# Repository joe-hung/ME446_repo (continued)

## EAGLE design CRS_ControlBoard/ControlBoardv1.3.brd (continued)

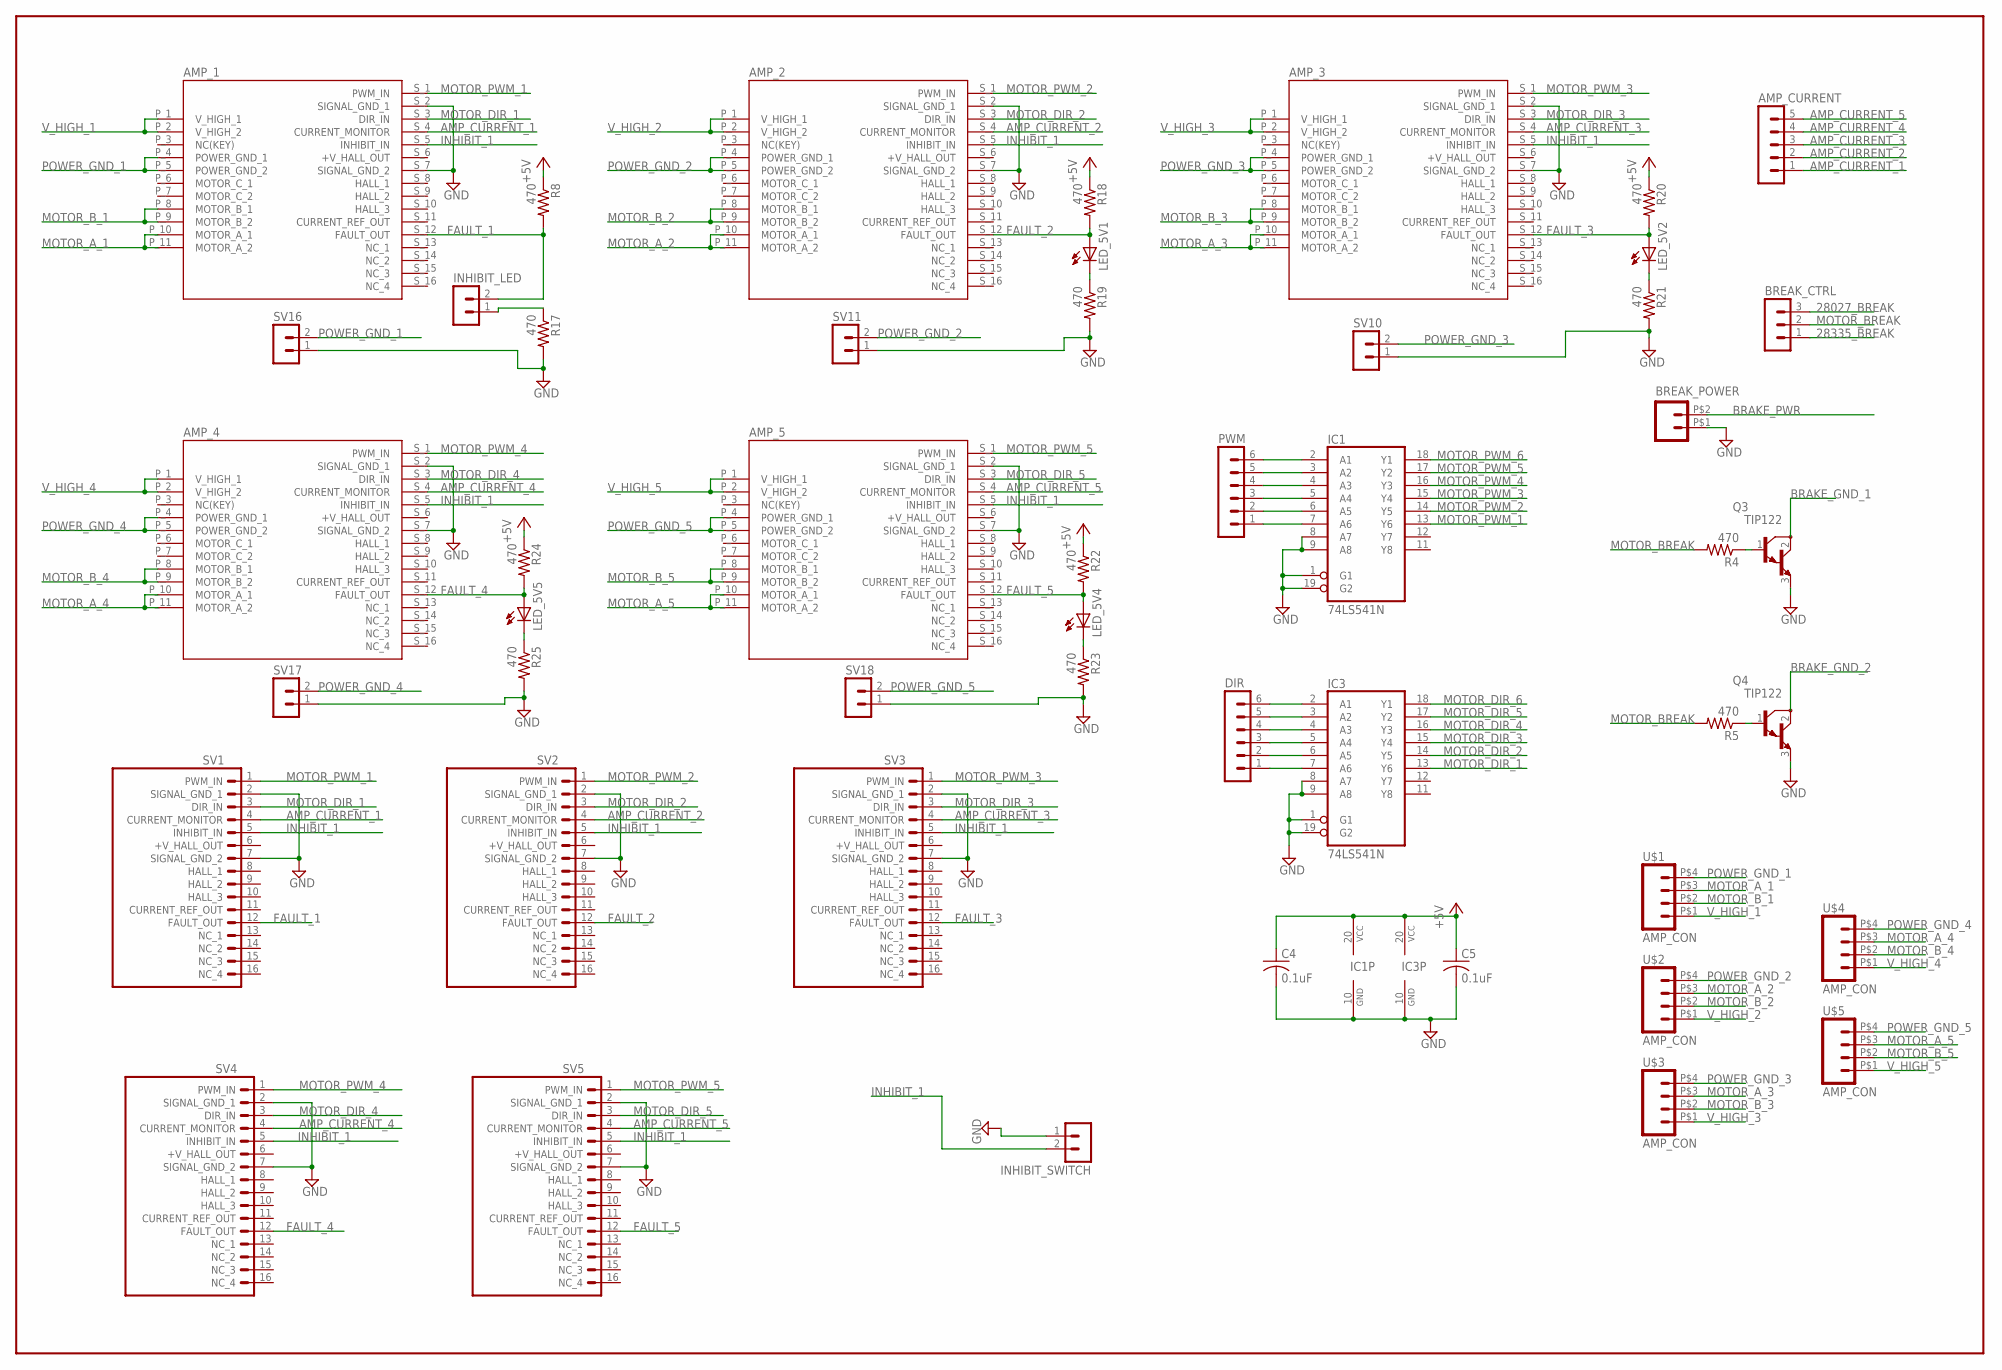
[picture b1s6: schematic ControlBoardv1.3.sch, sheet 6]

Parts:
AMP_1, AMP_2, AMP_3, AMP_4, AMP_5: AZBDC12A8THROUGH_HOLE; AZBDC12A8
AMP_CURRENT: MA05-1
BREAK_CTRL: MA03-1
BREAK_POWER: BREAK_POWER_CON
C4, C5: 0.1uF; C1206
DIR: MA06-1
IC1, IC3: 74LS541N; DIL20
INHIBIT_LED: MA02-1
INHIBIT_SWITCH: MA02-1
LED_5V1, LED_5V2, LED_5V4, LED_5V5: LED3MM
PWM: MA06-1
Q3, Q4: TIP122; TO220
R4, R5, R8, R17, R18, R19, R20, R21, R22, R23, R24, R25: 470; M1206
SV1, SV2, SV3, SV4, SV5: AMP_HEADER
SV10, SV11, SV16, SV17, SV18: MA02-1
U$1, U$2, U$3, U$4, U$5: AMP_CON; APM_CON

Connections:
28027_BREAK: BREAK_CTRL.3; also elsewhere on the board
28335_BREAK: BREAK_CTRL.1; also elsewhere on the board
+5V: C4.1, C5.1, IC1.20 (VCC), IC3.20 (VCC), R8.1, R18.1, R20.1, R22.1, R24.1; also elsewhere on the board
AMP_CURRENT_1: AMP_1.S_4 (CURRENT_MONITOR), AMP_CURRENT.1, SV1.4 (CURRENT_MONITOR)
AMP_CURRENT_2: AMP_2.S_4 (CURRENT_MONITOR), AMP_CURRENT.2, SV2.4 (CURRENT_MONITOR)
AMP_CURRENT_3: AMP_3.S_4 (CURRENT_MONITOR), AMP_CURRENT.3, SV3.4 (CURRENT_MONITOR)
AMP_CURRENT_4: AMP_4.S_4 (CURRENT_MONITOR), AMP_CURRENT.4, SV4.4 (CURRENT_MONITOR)
AMP_CURRENT_5: AMP_5.S_4 (CURRENT_MONITOR), AMP_CURRENT.5, SV5.4 (CURRENT_MONITOR)
BRAKE_GND_1: Q3.2 (C); also elsewhere on the board
BRAKE_GND_2: Q4.2 (C); also elsewhere on the board
BRAKE_PWR: BREAK_POWER.P$2; also elsewhere on the board
FAULT_1: AMP_1.S_12 (FAULT_OUT), INHIBIT_LED.2, R8.2, SV1.12 (FAULT_OUT)
FAULT_2: AMP_2.S_12 (FAULT_OUT), LED_5V1.A, R18.2, SV2.12 (FAULT_OUT)
FAULT_3: AMP_3.S_12 (FAULT_OUT), LED_5V2.A, R20.2, SV3.12 (FAULT_OUT)
FAULT_4: AMP_4.S_12 (FAULT_OUT), LED_5V5.A, R24.2, SV4.12 (FAULT_OUT)
FAULT_5: AMP_5.S_12 (FAULT_OUT), LED_5V4.A, R22.2, SV5.12 (FAULT_OUT)
GND: AMP_1.S_2 (SIGNAL_GND_1), AMP_1.S_7 (SIGNAL_GND_2), AMP_2.S_2 (SIGNAL_GND_1), AMP_2.S_7 (SIGNAL_GND_2), AMP_3.S_2 (SIGNAL_GND_1), AMP_3.S_7 (SIGNAL_GND_2), AMP_4.S_2 (SIGNAL_GND_1), AMP_4.S_7 (SIGNAL_GND_2), AMP_5.S_2 (SIGNAL_GND_1), AMP_5.S_7 (SIGNAL_GND_2), BREAK_POWER.P$1, C4.2, C5.2, IC1.1 (G1), IC1.8 (A7), IC1.9 (A8), IC1.10 (GND), IC1.19 (G2), IC3.1 (G1), IC3.8 (A7), IC3.9 (A8), IC3.10 (GND), IC3.19 (G2), INHIBIT_SWITCH.1, Q3.3 (E), Q4.3 (E), R17.2, R19.2, R21.2, R23.2, R25.2, SV1.2 (SIGNAL_GND_1), SV1.7 (SIGNAL_GND_2), SV2.2 (SIGNAL_GND_1), SV2.7 (SIGNAL_GND_2), SV3.2 (SIGNAL_GND_1), SV3.7 (SIGNAL_GND_2), SV4.2 (SIGNAL_GND_1), SV4.7 (SIGNAL_GND_2), SV5.2 (SIGNAL_GND_1), SV5.7 (SIGNAL_GND_2), SV10.1, SV11.1, SV16.1, SV17.1, SV18.1; also elsewhere on the board
INHIBIT_1: AMP_1.S_5 (INHIBIT_IN), AMP_2.S_5 (INHIBIT_IN), AMP_3.S_5 (INHIBIT_IN), AMP_4.S_5 (INHIBIT_IN), AMP_5.S_5 (INHIBIT_IN), INHIBIT_SWITCH.2, SV1.5 (INHIBIT_IN), SV2.5 (INHIBIT_IN), SV3.5 (INHIBIT_IN), SV4.5 (INHIBIT_IN), SV5.5 (INHIBIT_IN)
MOTOR_A_1: AMP_1.P_10 (MOTOR_A_1), AMP_1.P_11 (MOTOR_A_2), U$1.P$3
MOTOR_A_2: AMP_2.P_10 (MOTOR_A_1), AMP_2.P_11 (MOTOR_A_2), U$2.P$3
MOTOR_A_3: AMP_3.P_10 (MOTOR_A_1), AMP_3.P_11 (MOTOR_A_2), U$3.P$3
MOTOR_A_4: AMP_4.P_10 (MOTOR_A_1), AMP_4.P_11 (MOTOR_A_2), U$4.P$3
MOTOR_A_5: AMP_5.P_10 (MOTOR_A_1), AMP_5.P_11 (MOTOR_A_2), U$5.P$3
MOTOR_BREAK: BREAK_CTRL.2, R4.2, R5.2
MOTOR_B_1: AMP_1.P_8 (MOTOR_B_1), AMP_1.P_9 (MOTOR_B_2), U$1.P$2
MOTOR_B_2: AMP_2.P_8 (MOTOR_B_1), AMP_2.P_9 (MOTOR_B_2), U$2.P$2
MOTOR_B_3: AMP_3.P_8 (MOTOR_B_1), AMP_3.P_9 (MOTOR_B_2), U$3.P$2
MOTOR_B_4: AMP_4.P_8 (MOTOR_B_1), AMP_4.P_9 (MOTOR_B_2), U$4.P$2
MOTOR_B_5: AMP_5.P_8 (MOTOR_B_1), AMP_5.P_9 (MOTOR_B_2), U$5.P$2
MOTOR_DIR_1: AMP_1.S_3 (DIR_IN), IC3.13 (Y6), SV1.3 (DIR_IN)
MOTOR_DIR_2: AMP_2.S_3 (DIR_IN), IC3.14 (Y5), SV2.3 (DIR_IN)
MOTOR_DIR_3: AMP_3.S_3 (DIR_IN), IC3.15 (Y4), SV3.3 (DIR_IN)
MOTOR_DIR_4: AMP_4.S_3 (DIR_IN), IC3.16 (Y3), SV4.3 (DIR_IN)
MOTOR_DIR_5: AMP_5.S_3 (DIR_IN), IC3.17 (Y2), SV5.3 (DIR_IN)
MOTOR_DIR_6: IC3.18 (Y1)
MOTOR_PWM_1: AMP_1.S_1 (PWM_IN), IC1.13 (Y6), SV1.1 (PWM_IN)
MOTOR_PWM_2: AMP_2.S_1 (PWM_IN), IC1.14 (Y5), SV2.1 (PWM_IN)
MOTOR_PWM_3: AMP_3.S_1 (PWM_IN), IC1.15 (Y4), SV3.1 (PWM_IN)
MOTOR_PWM_4: AMP_4.S_1 (PWM_IN), IC1.16 (Y3), SV4.1 (PWM_IN)
MOTOR_PWM_5: AMP_5.S_1 (PWM_IN), IC1.17 (Y2), SV5.1 (PWM_IN)
MOTOR_PWM_6: IC1.18 (Y1)
unnamed: IC1.7 (A6), PWM.1
unnamed: IC1.6 (A5), PWM.2
unnamed: DIR.1, IC3.7 (A6)
unnamed: Q3.1 (B), R4.1
unnamed: DIR.2, IC3.6 (A5)
unnamed: DIR.3, IC3.5 (A4)
unnamed: DIR.4, IC3.4 (A3)
unnamed: IC1.5 (A4), PWM.3
unnamed: IC1.4 (A3), PWM.4
unnamed: IC1.3 (A2), PWM.5
unnamed: IC1.2 (A1), PWM.6
unnamed: INHIBIT_LED.1, R17.1
unnamed: Q4.1 (B), R5.1
unnamed: DIR.6, IC3.2 (A1)
unnamed: DIR.5, IC3.3 (A2)
unnamed: LED_5V1.K (C), R19.1
unnamed: LED_5V2.K (C), R21.1
unnamed: LED_5V4.K (C), R23.1
unnamed: LED_5V5.K (C), R25.1
POWER_GND_1: AMP_1.P_4 (POWER_GND_1), AMP_1.P_5 (POWER_GND_2), SV16.2, U$1.P$4
POWER_GND_2: AMP_2.P_4 (POWER_GND_1), AMP_2.P_5 (POWER_GND_2), SV11.2, U$2.P$4
POWER_GND_3: AMP_3.P_4 (POWER_GND_1), AMP_3.P_5 (POWER_GND_2), SV10.2, U$3.P$4
POWER_GND_4: AMP_4.P_4 (POWER_GND_1), AMP_4.P_5 (POWER_GND_2), SV17.2, U$4.P$4
POWER_GND_5: AMP_5.P_4 (POWER_GND_1), AMP_5.P_5 (POWER_GND_2), SV18.2, U$5.P$4
V_HIGH_1: AMP_1.P_1 (V_HIGH_1), AMP_1.P_2 (V_HIGH_2), U$1.P$1
V_HIGH_2: AMP_2.P_1 (V_HIGH_1), AMP_2.P_2 (V_HIGH_2), U$2.P$1
V_HIGH_3: AMP_3.P_1 (V_HIGH_1), AMP_3.P_2 (V_HIGH_2), U$3.P$1
V_HIGH_4: AMP_4.P_1 (V_HIGH_1), AMP_4.P_2 (V_HIGH_2), U$4.P$1
V_HIGH_5: AMP_5.P_1 (V_HIGH_1), AMP_5.P_2 (V_HIGH_2), U$5.P$1

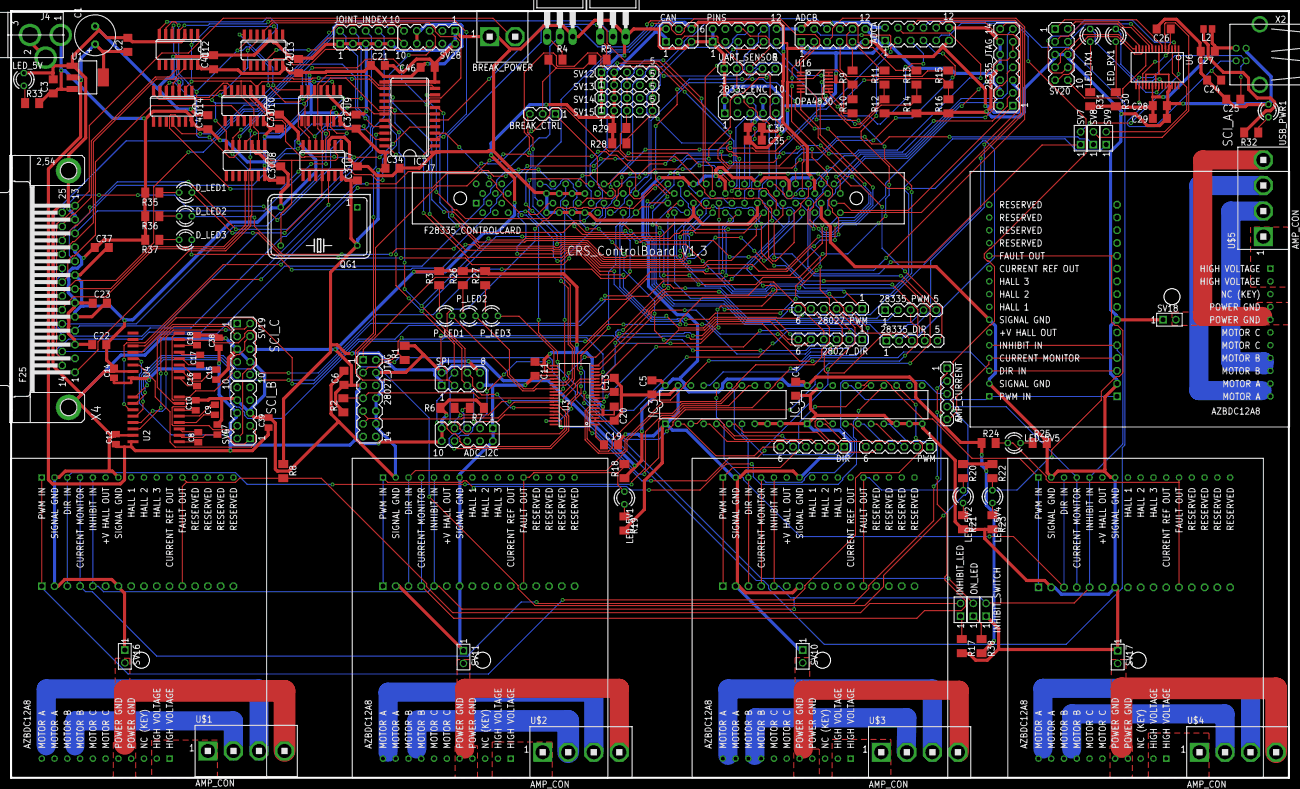
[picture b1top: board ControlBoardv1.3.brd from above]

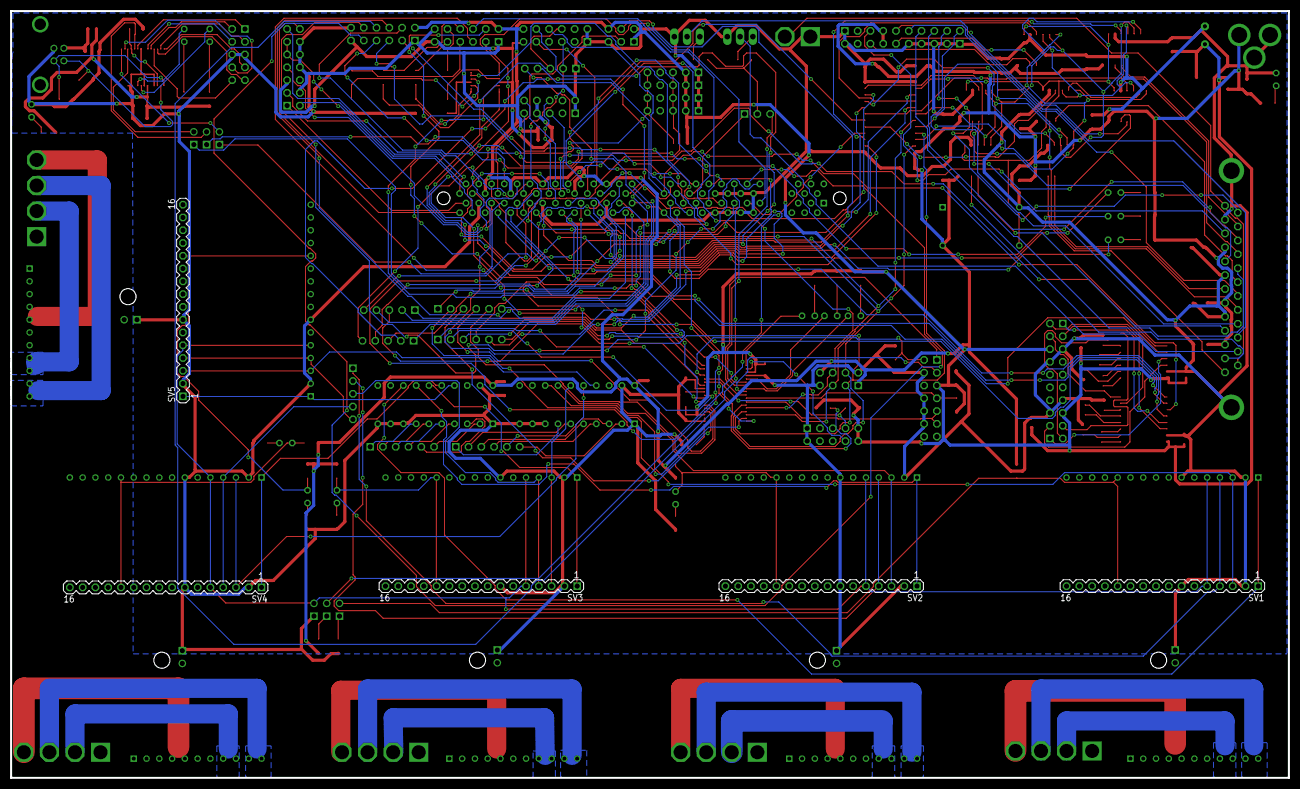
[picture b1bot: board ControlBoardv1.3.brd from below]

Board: 2 copper layers, 254.0 x 152.4 mm, 172 parts (10 on the bottom side), 249 nets.

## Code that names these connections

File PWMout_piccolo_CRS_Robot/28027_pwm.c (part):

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	case EPWM1:
		
		EALLOW;
		GpioCtrlRegs.GPAMUX1.bit.GPIO0 = 1;
		EDIS;

		EPwm1Regs.TBPRD = PWM_PR;  // Set to Period for 20Khz carrier
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	case EPWM2:
		
		EALLOW;
		GpioCtrlRegs.GPAMUX1.bit.GPIO2 = 1;
		EDIS;

		EPwm2Regs.TBPRD = PWM_PR;  // Set to Period for 20Khz carrier
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	case EPWM3:
		
		EALLOW;
		GpioCtrlRegs.GPAMUX1.bit.GPIO4 = 1;
		EDIS;

		EPwm3Regs.TBPRD = PWM_PR;  // Set to Period for 20Khz carrier
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	case EPWM4:
		
		EALLOW;
		//GpioCtrlRegs.GPAMUX1.bit.GPIO6 = 1;
		EDIS;

		EPwm4Regs.TBPRD = PWM_PR;  // Set to Period for 20Khz carrier
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
	case EPWM1:
		EALLOW;
		GpioCtrlRegs.GPAMUX1.bit.GPIO0 = 0;
		GpioCtrlRegs.GPAMUX1.bit.GPIO1 = 0;
		GpioDataRegs.GPACLEAR.bit.GPIO0 = 0;
		GpioDataRegs.GPACLEAR.bit.GPIO1 = 0;
		GpioCtrlRegs.GPADIR.bit.GPIO0 = 1;
		GpioCtrlRegs.GPADIR.bit.GPIO1 = 1;
		EDIS;
		

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		EPwm1Regs.AQCTLB.bit.PRD = 2; // Set EPWM1B pin when CTR=PRD

		EALLOW;
		GpioCtrlRegs.GPAMUX1.bit.GPIO0 = 1;
		GpioCtrlRegs.GPAMUX1.bit.GPIO1 = 1;
		EDIS;

		break;
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/*	case EPWM2:
		
		EALLOW;
		GpioCtrlRegs.GPAMUX1.bit.GPIO2 = 1;
		EDIS;

		EPwm2Regs.TBPRD = PWM_PR;  // Set to Period for 20Khz carrier
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	case EPWM3:
		
		EALLOW;
		GpioCtrlRegs.GPAMUX1.bit.GPIO4 = 1;
		EDIS;

		EPwm3Regs.TBPRD = PWM_PR;  // Set to Period for 20Khz carrier
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	case EPWM4:
		
		EALLOW;
		GpioCtrlRegs.GPAMUX1.bit.GPIO6 = 1;
		EDIS;

		EPwm4Regs.TBPRD = PWM_PR;  // Set to Period for 20Khz carrier
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		EALLOW;

		//PWM pins
		GpioCtrlRegs.GPAMUX1.bit.GPIO0 = 1; //set to 1 for pwm
		//GpioDataRegs.GPACLEAR.bit.GPIO0 = 0;
		//GpioCtrlRegs.GPADIR.bit.GPIO0 = 0;

		GpioCtrlRegs.GPAMUX1.bit.GPIO1 = 1; //set to 1 for pwm
		//GpioDataRegs.GPACLEAR.bit.GPIO1 = 0;
		//GpioCtrlRegs.GPADIR.bit.GPIO1 = 0;

		//DIR Pins
		GpioCtrlRegs.GPAMUX1.bit.GPIO6 = 0;
		GpioCtrlRegs.GPADIR.bit.GPIO6 = 1;
		GpioCtrlRegs.GPAMUX1.bit.GPIO7 = 0;
		GpioCtrlRegs.GPADIR.bit.GPIO7 = 1;

		EDIS;

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	case EPWM2:

		EALLOW;
		GpioCtrlRegs.GPAMUX1.bit.GPIO2 = 1; //set to 1 for pwm
		//GpioDataRegs.GPACLEAR.bit.GPIO2 = 0;
		//GpioCtrlRegs.GPADIR.bit.GPIO2 = 0;

		GpioCtrlRegs.GPAMUX1.bit.GPIO3 = 1; //set to 1 for pwm
		//GpioDataRegs.GPACLEAR.bit.GPIO3 = 0;
		//GpioCtrlRegs.GPADIR.bit.GPIO3 = 0;

		//DIR Pins
		GpioCtrlRegs.GPAMUX1.bit.GPIO12 = 0;
		GpioCtrlRegs.GPADIR.bit.GPIO12 = 1;
		GpioCtrlRegs.AIOMUX1.bit.AIO4 = 1;
		GpioCtrlRegs.AIODIR.bit.AIO4 = 1;

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	case EPWM3:

		EALLOW;
		GpioCtrlRegs.GPAMUX1.bit.GPIO4 = 1; //set to 1 for pwm
		//GpioDataRegs.GPACLEAR.bit.GPIO4 = 0;
		//GpioCtrlRegs.GPADIR.bit.GPIO4 = 0;

		GpioCtrlRegs.GPAMUX1.bit.GPIO5 = 1; //set to 1 for pwm
		//GpioDataRegs.GPACLEAR.bit.GPIO5 = 0;
		//GpioCtrlRegs.GPADIR.bit.GPIO5 = 0;

		//PWM Pins
		GpioCtrlRegs.AIOMUX1.bit.AIO6 = 1;
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		EPwm1Regs.CMPA.half.CMPA = val;
		//EPwm1Regs.CMPA.half.CMPAHR = dec;
		if (u >= 0) {
			GpioDataRegs.GPASET.bit.GPIO6 = 1;
		} else {
			GpioDataRegs.GPACLEAR.bit.GPIO6 = 1;
		}
		break;

	case (0x2):
		EPwm1Regs.CMPB = val;
		if (u >= 0) {
			GpioDataRegs.GPASET.bit.GPIO7 = 1;
		} else {
			GpioDataRegs.GPACLEAR.bit.GPIO7 = 1;
		}
		break;

//		EPwm2Regs.CMPA.half.CMPA = val;
//		EPwm2Regs.CMPA.half.CMPAHR = dec;
//		if (u >= 0) {
//			GpioDataRegs.GPASET.bit.GPIO7 = 1;   //High Res PWM
//		} else {
//			GpioDataRegs.GPACLEAR.bit.GPIO7 = 1;
//		}
//
//	break;
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	case (0x3):
			EPwm2Regs.CMPA.half.CMPA = val;
			if (u >= 0) {
				GpioDataRegs.GPASET.bit.GPIO12 = 1;
			} else {
				GpioDataRegs.GPACLEAR.bit.GPIO12 = 1;
			}

		break;
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//		EPwm3Regs.CMPA.half.CMPA = val;
//		EPwm3Regs.CMPA.half.CMPAHR = dec;
//		if (u >= 0) {
//			GpioDataRegs.GPASET.bit.GPIO12 = 1;
//		} else {
//			GpioDataRegs.GPACLEAR.bit.GPIO12 = 1;
//		}
//
//	break;
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
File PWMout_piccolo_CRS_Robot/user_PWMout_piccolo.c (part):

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void Debug3Bits(unsigned int bits) {
	switch (bits) {
	case 0:
		GpioDataRegs.GPACLEAR.bit.GPIO0 = 1;
		GpioDataRegs.GPACLEAR.bit.GPIO2 = 1;
		GpioDataRegs.GPACLEAR.bit.GPIO5 = 1;
		break;
	case 1:
		GpioDataRegs.GPASET.bit.GPIO0 = 1;
		GpioDataRegs.GPACLEAR.bit.GPIO2 = 1;
		GpioDataRegs.GPACLEAR.bit.GPIO5 = 1;
		break;
	case 2:
		GpioDataRegs.GPACLEAR.bit.GPIO0 = 1;
		GpioDataRegs.GPASET.bit.GPIO2 = 1;
		GpioDataRegs.GPACLEAR.bit.GPIO5 = 1;

		break;
	case 3:
		GpioDataRegs.GPASET.bit.GPIO0 = 1;
		GpioDataRegs.GPASET.bit.GPIO2 = 1;
		GpioDataRegs.GPACLEAR.bit.GPIO5 = 1;

		break;
	case 4:
		GpioDataRegs.GPACLEAR.bit.GPIO0 = 1;
		GpioDataRegs.GPACLEAR.bit.GPIO2 = 1;
		GpioDataRegs.GPASET.bit.GPIO5 = 1;

		break;
	case 5:
		GpioDataRegs.GPASET.bit.GPIO0 = 1;
		GpioDataRegs.GPACLEAR.bit.GPIO2 = 1;
		GpioDataRegs.GPASET.bit.GPIO5 = 1;

		break;
	case 6:
		GpioDataRegs.GPACLEAR.bit.GPIO0 = 1;
		GpioDataRegs.GPASET.bit.GPIO2 = 1;
		GpioDataRegs.GPASET.bit.GPIO5 = 1;

		break;
	case 7:
		GpioDataRegs.GPASET.bit.GPIO0 = 1;
		GpioDataRegs.GPASET.bit.GPIO2 = 1;
		GpioDataRegs.GPASET.bit.GPIO5 = 1;

		break;
	default:
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
	EALLOW;

		GpioCtrlRegs.GPBMUX1.bit.GPIO34 = 0;
		GpioDataRegs.GPBCLEAR.bit.GPIO34 = 1;
		GpioCtrlRegs.GPBDIR.bit.GPIO34 = 1;

		GpioCtrlRegs.GPAMUX1.bit.GPIO3 = 0;
		GpioDataRegs.GPACLEAR.bit.GPIO3 = 0;
		GpioCtrlRegs.GPADIR.bit.GPIO3 = 1;

		// Code for sensing Magnet  Commented out to use GPIO5 as debug output
//		GpioCtrlRegs.GPAMUX1.bit.GPIO5 = 0;
//		GpioCtrlRegs.GPADIR.bit.GPIO5 = 0;  // input
//		GpioCtrlRegs.GPAPUD.bit.GPIO5 = 0; // enable pullup on GPIO5
//		GpioCtrlRegs.GPAQSEL1.bit.GPIO5 = 0x2;  // qual on 6 samples
//		GpioCtrlRegs.GPACTRL.bit.QUALPRD0 = 0x20;  // QualPeriod of 32*Sysclkout

		GpioCtrlRegs.GPAMUX1.bit.GPIO0 = 0;
		GpioDataRegs.GPACLEAR.bit.GPIO0 = 1;
		GpioCtrlRegs.GPADIR.bit.GPIO0 = 1;

		GpioCtrlRegs.GPAMUX1.bit.GPIO2 = 0;
		GpioDataRegs.GPACLEAR.bit.GPIO2 = 1;
		GpioCtrlRegs.GPADIR.bit.GPIO2 = 1;

		GpioCtrlRegs.GPAMUX1.bit.GPIO5 = 0;
		GpioDataRegs.GPACLEAR.bit.GPIO5 = 1;
		GpioCtrlRegs.GPADIR.bit.GPIO5 = 1;

		GpioCtrlRegs.AIOMUX1.bit.AIO10 = 1;
		GpioCtrlRegs.AIOMUX1.bit.AIO2 = 1;
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		EALLOW;

			// CS pins GPIOs
			//GpioCtrlRegs.GPAMUX1.bit.GPIO6 = 0;
			GpioCtrlRegs.GPAMUX2.bit.GPIO19 = 0;
			// CS pins Outputs
			//GpioCtrlRegs.GPADIR.bit.GPIO6 = 1;
			GpioCtrlRegs.GPADIR.bit.GPIO19 = 1;
			// CS start hi
			//GpioDataRegs.GPASET.bit.GPIO6 = 1;
			GpioDataRegs.GPASET.bit.GPIO19 = 1;
		
		EDIS;

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		if(errorbits & 0x0400) //spi error
		{

			GpioDataRegs.GPBCLEAR.bit.GPIO34 = 1;	// Set LED1

		}
		else{
			GpioDataRegs.GPBSET.bit.GPIO34 = 1; // Clear LED1
		}
		if(errorbits & 0x0100) //lg error
		{
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		{

			GpioDataRegs.AIOCLEAR.bit.AIO2 = 1;	// Set LED4
			GpioDataRegs.GPBCLEAR.bit.GPIO34 = 1;	// Set LED1
			GpioDataRegs.AIOCLEAR.bit.AIO10 = 1;	// Set LED2

		}
		else{

			if(errorflag_spi == 0){
				GpioDataRegs.GPBSET.bit.GPIO34 = 1; // Clear LED1				//Double checking these LEDs since they are shared with other errors.
			}
			if(errorflag_lg == 0){
				GpioDataRegs.AIOSET.bit.AIO10 = 1; //Clear LED2
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
//	if (StartUsonic == 1) {
//		Debug3Bits(6);
//		GpioDataRegs.GPASET.bit.GPIO3 = 1;	// pulse GPIO34 (Ultrasonic RX1) high for 1ms
//		StartUsonic = 2;
//	} else if (StartUsonic == 2) {
//		Debug3Bits(7);
//		GpioDataRegs.GPACLEAR.bit.GPIO3 = 1;
//		StartUsonic = 0;
//		TXUsonic = 1;
//	}
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
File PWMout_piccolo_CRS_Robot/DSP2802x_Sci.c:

// TI File $Revision: /main/1 $
// Checkin $Date: August 14, 2008   16:58:46 $
//###########################################################################
//
// FILE:	DSP2802x_Sci.c
//
// TITLE:	DSP2802x SCI Initialization & Support Functions.
//
//###########################################################################
// $TI Release: 2802x C/C++ Header Files V1.26 $
// $Release Date: February 2, 2010 $
//###########################################################################

#include "DSP2802x_Device.h"     // DSP2802x Headerfile Include File
#include "DSP2802x_Examples.h"   // DSP2802x Examples Include File

//---------------------------------------------------------------------------
// InitSci:
//---------------------------------------------------------------------------
// This function initializes the SCI(s) to a known state.
//
void InitSci(void)
{
	// Initialize SCI-A:

	//tbd...

}

//---------------------------------------------------------------------------
// Example: InitSciGpio:
//---------------------------------------------------------------------------
// This function initializes GPIO pins to function as SCI pins
//
// Each GPIO pin can be configured as a GPIO pin or up to 3 different
// peripheral functional pins. By default all pins come up as GPIO
// inputs after reset.
//
// Caution:
// Only one GPIO pin should be enabled for SCITXDA/B operation.
// Only one GPIO pin shoudl be enabled for SCIRXDA/B operation.
// Comment out other unwanted lines.

void InitSciGpio()
{
   InitSciaGpio();
}

void InitSciaGpio()
{
   EALLOW;

/* Enable internal pull-up for the selected pins */
/* Disable internal pull-up for the selected output pins
   to reduce power consumption. */
// Pull-ups can be enabled or disabled disabled by the user.

	GpioCtrlRegs.GPAPUD.bit.GPIO28 = 0;    // Enable pull-up for GPIO28 (SCIRXDA)
//	GpioCtrlRegs.GPAPUD.bit.GPIO19 = 0;    // Enable pull-up for GPIO19 (SCIRXDA)
//	GpioCtrlRegs.GPAPUD.bit.GPIO7 = 0;     // Enable pull-up for GPIO7  (SCIRXDA)

	GpioCtrlRegs.GPAPUD.bit.GPIO29 = 1;	   // Disable pull-up for GPIO29 (SCITXDA)
//	GpioCtrlRegs.GPAPUD.bit.GPIO18 = 1;	   // Disable pull-up for GPIO18 (SCITXDA)
//	GpioCtrlRegs.GPAPUD.bit.GPIO12 = 1;	   // Disable pull-up for GPIO12 (SCITXDA)

/* Set qualification for selected pins to asynch only */
// Inputs are synchronized to SYSCLKOUT by default.
// This will select asynch (no qualification) for the selected pins.

	GpioCtrlRegs.GPAQSEL2.bit.GPIO28 = 3;  // Asynch input GPIO28 (SCIRXDA)
//	GpioCtrlRegs.GPAQSEL2.bit.GPIO19 = 3;  // Asynch input GPIO19 (SCIRXDA)
//	GpioCtrlRegs.GPAQSEL1.bit.GPIO7 = 3;   // Asynch input GPIO7 (SCIRXDA)

/* Configure SCI-A pins using GPIO regs*/
// This specifies which of the possible GPIO pins will be SCI functional pins.

	GpioCtrlRegs.GPAMUX2.bit.GPIO28 = 1;   // Configure GPIO28 for SCIRXDA operation
//	GpioCtrlRegs.GPAMUX2.bit.GPIO19 = 2;   // Configure GPIO19 for SCIRXDA operation
//	GpioCtrlRegs.GPAMUX1.bit.GPIO7 = 2;    // Configure GPIO7  for SCIRXDA operation

	GpioCtrlRegs.GPAMUX2.bit.GPIO29 = 1;   // Configure GPIO29 for SCITXDA operation
//	GpioCtrlRegs.GPAMUX2.bit.GPIO18 = 2;   // Configure GPIO18 for SCITXDA operation
//	GpioCtrlRegs.GPAMUX1.bit.GPIO12 = 2;   // Configure GPIO12 for SCITXDA operation

    EDIS;
}

//===========================================================================
// End of file.
//===========================================================================

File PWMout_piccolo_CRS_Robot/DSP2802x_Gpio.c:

// TI File $Revision: /main/1 $
// Checkin $Date: August 14, 2008   16:58:31 $
//###########################################################################
//
// FILE:	DSP2802x_Gpio.c
//
// TITLE:	DSP2802x General Purpose I/O Initialization & Support Functions.
//
//###########################################################################
// $TI Release: 2802x C/C++ Header Files V1.26 $
// $Release Date: February 2, 2010 $
//###########################################################################

#include "DSP2802x_Device.h"     // DSP2802x Headerfile Include File
#include "DSP2802x_Examples.h"   // DSP2802x Examples Include File

//---------------------------------------------------------------------------
// InitGpio:
//---------------------------------------------------------------------------
// This function initializes the Gpio to a known (default) state.
//
// For more details on configuring GPIO's as peripheral functions,
// refer to the individual peripheral examples and/or GPIO setup example.
void InitGpio(void)
{
   EALLOW;

   // Each GPIO pin can be:
   // a) a GPIO input/output
   // b) peripheral function 1
   // c) peripheral function 2
   // d) peripheral function 3
   // By default, all are GPIO Inputs
   GpioCtrlRegs.GPAMUX1.all = 0x0000;     // GPIO functionality GPIO0-GPIO15
   GpioCtrlRegs.GPAMUX2.all = 0x0000;     // GPIO functionality GPIO16-GPIO31
   GpioCtrlRegs.GPBMUX1.all = 0x0000;     // GPIO functionality GPIO32-GPIO34
   GpioCtrlRegs.AIOMUX1.all = 0x0000;     // Dig.IO funct. applies to AIO2,4,6,10,12,14

   GpioCtrlRegs.GPADIR.all = 0x0000;      // GPIO0-GPIO31 are GP inputs
   GpioCtrlRegs.GPBDIR.all = 0x0000;      // GPIO32-GPIO34 are inputs
   GpioCtrlRegs.AIODIR.all = 0x0000;      // AIO2,4,6,19,12,14 are digital inputs

   // Each input can have different qualification
   // a) input synchronized to SYSCLKOUT
   // b) input qualified by a sampling window
   // c) input sent asynchronously (valid for peripheral inputs only)
   GpioCtrlRegs.GPAQSEL1.all = 0x0000;    // GPIO0-GPIO15 Synch to SYSCLKOUT
   GpioCtrlRegs.GPAQSEL2.all = 0x0000;    // GPIO16-GPIO31 Synch to SYSCLKOUT
   GpioCtrlRegs.GPBQSEL1.all = 0x0000;    // GPIO32-GPIO34 Synch to SYSCLKOUT

   // Pull-ups can be enabled or disabled.
   GpioCtrlRegs.GPAPUD.all = 0x0000;      // Pullup's enabled GPIO0-GPIO31
   GpioCtrlRegs.GPBPUD.all = 0x0000;      // Pullup's enabled GPIO32-GPIO34
   //GpioCtrlRegs.GPAPUD.all = 0xFFFF;    // Pullup's disabled GPIO0-GPIO31
   //GpioCtrlRegs.GPBPUD.all = 0xFFFF;    // Pullup's disabled GPIO32-GPIO34
   EDIS;

}

//===========================================================================
// End of file.
//===========================================================================

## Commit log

2022-10-19 First Commit Need to add LabStarter and check Piccolo Build
2022-10-19 Added DSP/BIOS install Notes
2022-10-19 Got PWMout_piccolo to compile
2022-10-19 Updated gitignore
2023-01-05 Merging with the merging branch
2023-01-05 Fixed warning about a directory
2023-01-05 Fix starter for ME446
2023-01-05 Adde COM1 to simulink
2023-01-05 Got rid of a UARTPrint in crs
2023-01-06 New Matlab commands working
2023-01-09 Updates to Matlab Commands
2023-01-10 Get Repo ready for the semester
2023-01-13 Added small fixes to Matlab commands
2023-01-20 Added README.md
2023-01-27 LAB1
2023-02-03 lab1-2
2023-02-10 LAB1-3
2023-02-17 LAB2-1
2023-02-24 LAB2-2
2023-03-03 lab2-3
2023-03-10 lab2-4
2023-03-19 LAB2 final
2023-03-24 LAB3-1
2023-03-31 Lab3-2
2023-04-07 LAB_4_1
2023-04-14 Lab4_f
2023-04-21 Lab4_comment
2023-04-21 Project_4/21
2023-04-28 project_04_28
2023-05-04 project_final
2023-05-05 project_comment
2023-05-05 project_comment_2
2023-05-05 project_comment_3
